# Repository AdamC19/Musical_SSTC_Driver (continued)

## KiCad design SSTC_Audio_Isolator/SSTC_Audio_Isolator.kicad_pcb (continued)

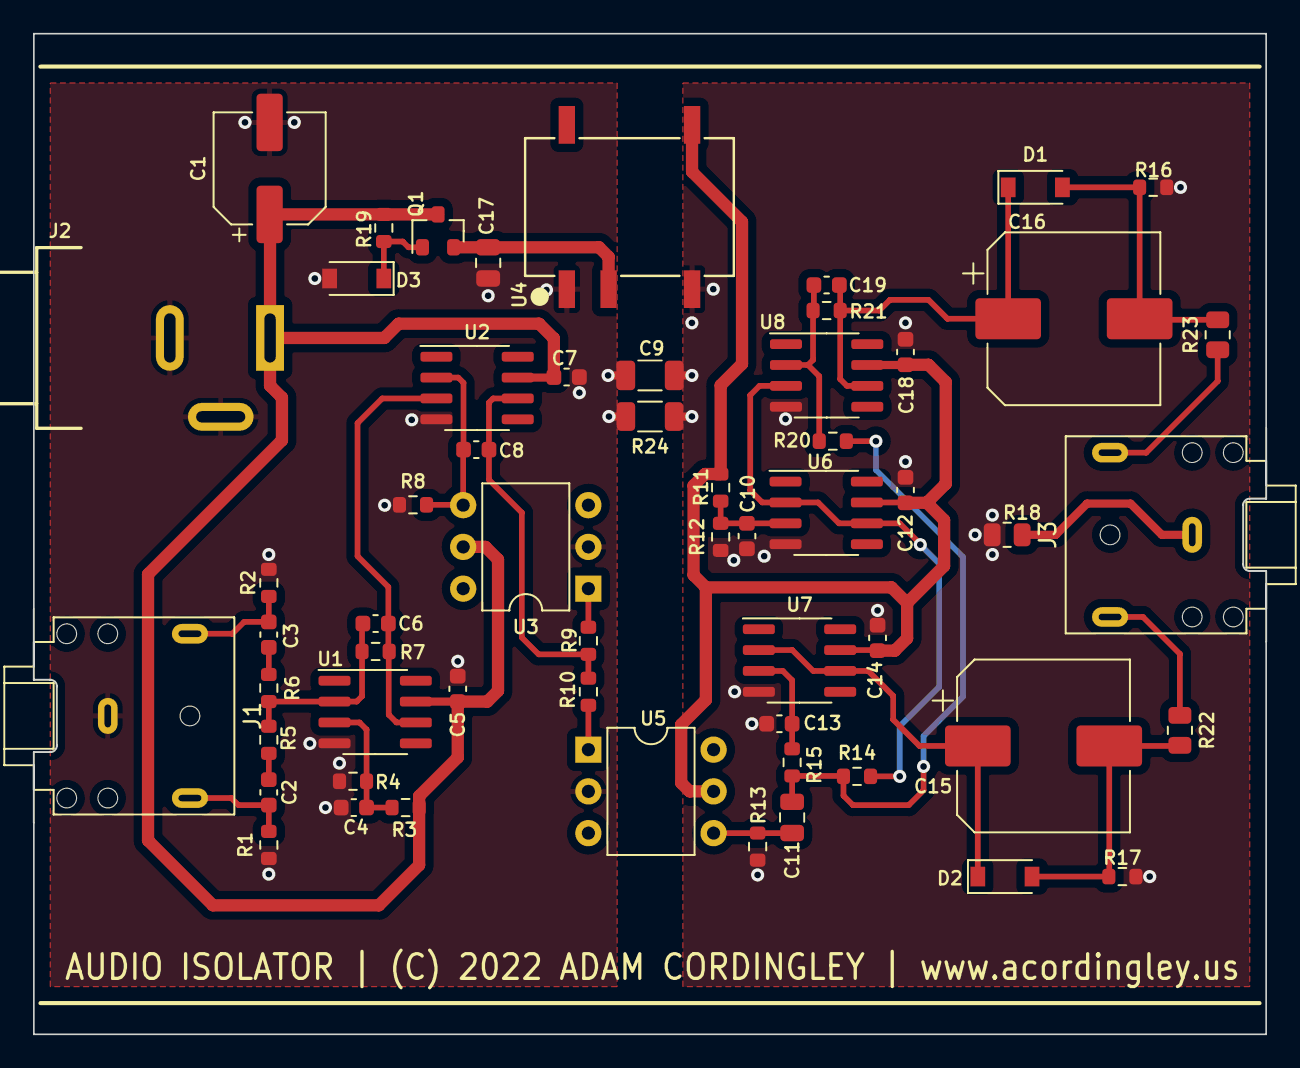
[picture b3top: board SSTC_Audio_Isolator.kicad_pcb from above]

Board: 2 copper layers, 75.0 x 60.9 mm, 58 parts (0 on the bottom side), 30 nets.

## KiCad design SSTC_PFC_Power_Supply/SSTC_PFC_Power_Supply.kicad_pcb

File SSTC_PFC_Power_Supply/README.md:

# APFC AC-DC Power Supply
This is an AC-to-DC power supply with Active Power Factor Correction (APFC). It takes in 120V AC and converts it to ~500V DC. It's designed to supply a maximum current of 1.8A, so about 900W. In case it needs to be said, this supply is dangerous! Don't build it unless you understand the risks and know how to mitigate them.

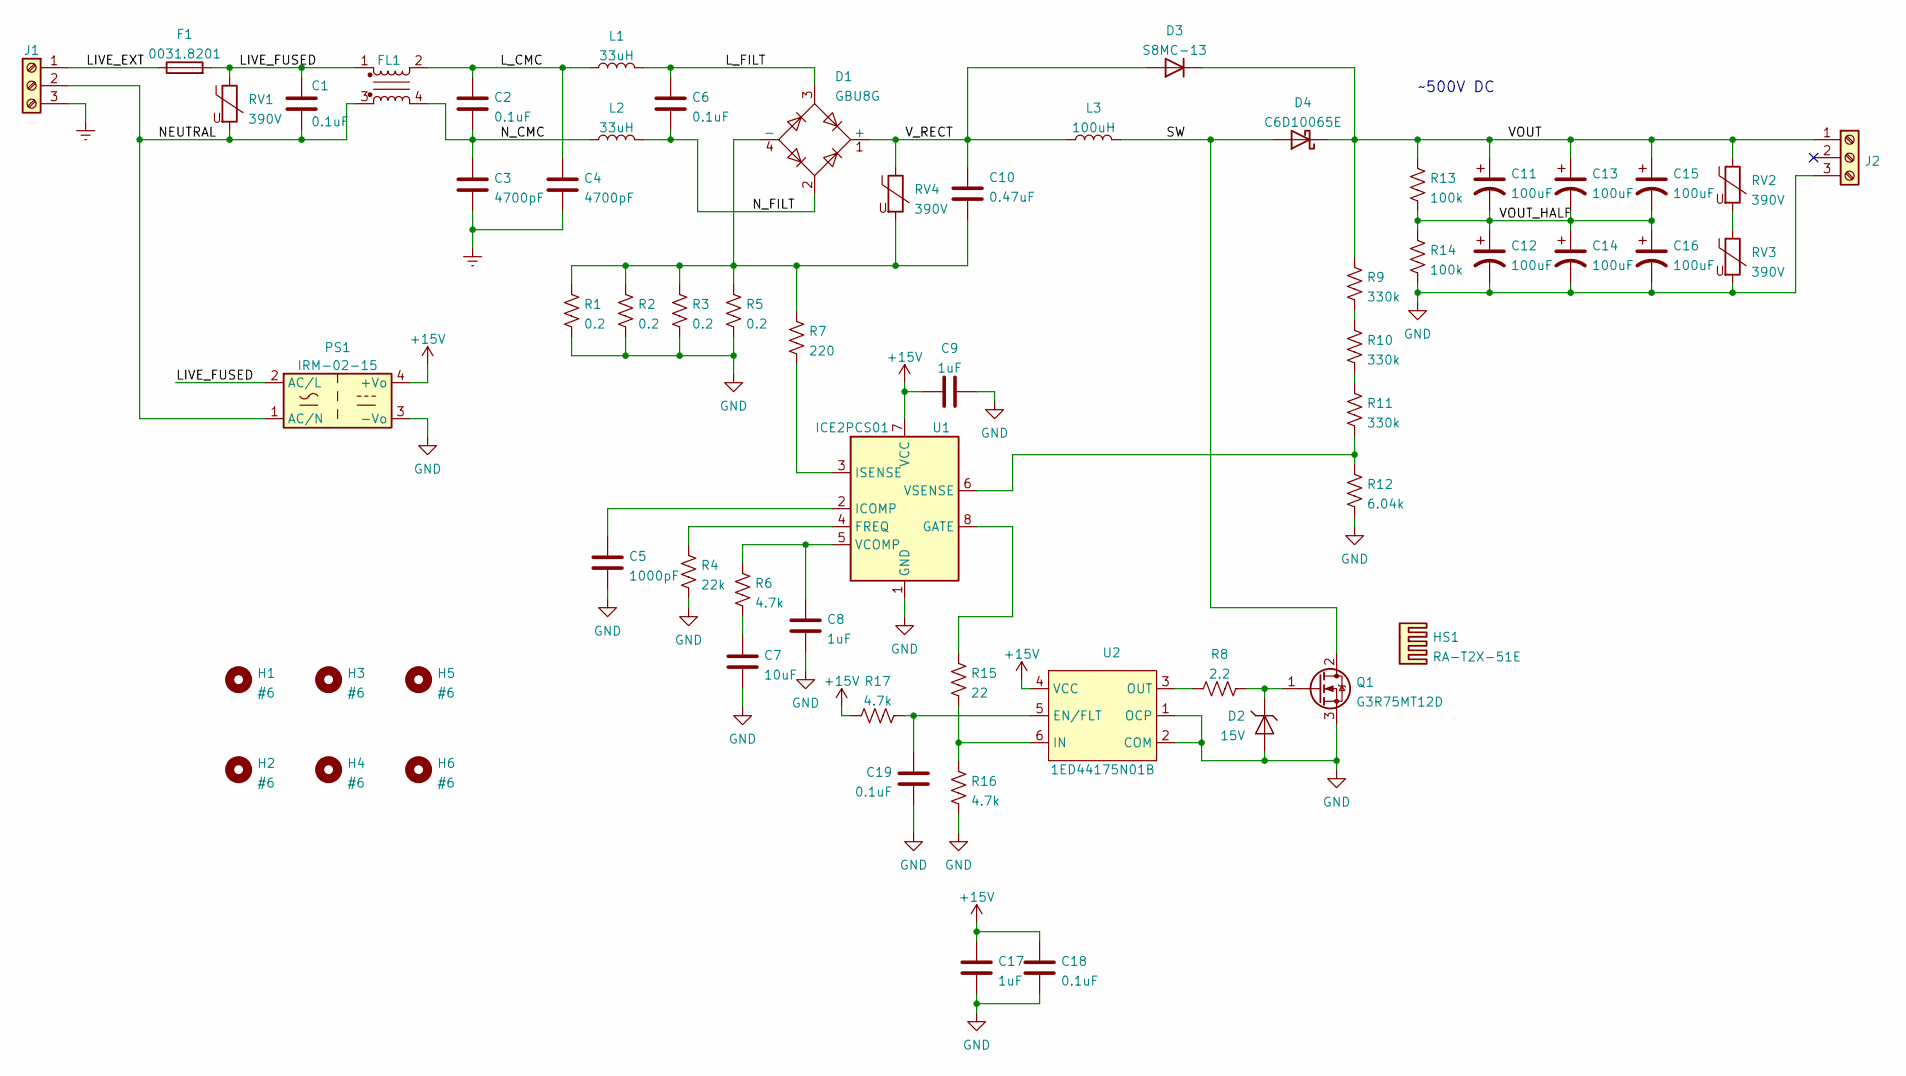
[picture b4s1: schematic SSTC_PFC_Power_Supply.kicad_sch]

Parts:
C1, C2, C6: 0.1uF; C_Rect_L18.0mm_W6.0mm_P15.00mm_FKS3_FKP3; MFG_PN PHE840MB6100MB05R17
C3, C4: 4700pF; C_Rect_L13.0mm_W4.0mm_P10.00mm_FKS3_FKP3_MKS4; MFG_PN R75PF1470AA01J
C5: 1000pF; C_0805_2012Metric
C7: 10uF; C_1206_3216Metric
C8, C9, C17: 1uF; C_0805_2012Metric
C10: 0.47uF; C_Rect_L18.0mm_W9.0mm_P15.00mm_FKS3_FKP3; MFG_PN B32922C3474K189
C11, C12, C13, C14, C15, C16: 100uF; CP_Radial_D18.0mm_P7.50mm; MFG_PN 450BXW100MEFR18X30
C18, C19: 0.1uF; C_0603_1608Metric
D1: GBU8G; Diode_Bridge_Vishay_GBU
D2: 15V; D_SOD-123
D3: S8MC-13; D_SMC; MFG_PN S8MC-13
D4: C6D10065E; TO-252-2_TabPin1_HV; MFG_PN C6D10065E
F1: 0031.8201; Fuseholder_Cylinder-5x20mm_Schurter_0031_8201_Horizontal_Op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; MFG_PN 0031.8201
FL1: 744824101; Weurth_WE-CMB; MFG_PN 744824101
H1, H2, H3, H4, H5, H6: #6; MountingHole_3.7mm_Pad
HS1: RA-T2X-51E; Ohmite_RA-T2X-51E; MFG_PN RA-T2X-51E
J1, J2: 1766246; PhoenixContact_GMSTBA_2,5_3-G-7,62_1x03_P7.62mm_Horizontal; MFG_PN 1766246
L1, L2: 33uH; L_Wuerth_HCI-2212; MFG_PN 74435583300
L3: 100uH; L_Bourns_1140-101K-RC; MFG_PN 1140-101K-RC
PS1: IRM-02-15; Converter_ACDC_MeanWell_IRM-02-xx_THT
Q1: G3R75MT12D; TO-247-3_Vertical; MFG_PN G3R75MT12D
R1, R2, R3, R5: 0.2; R_2512_6332Metric_High_Power; MFG_PN TLRP3A30CR200FTE
R4: 22k; R_0805_2012Metric
R6, R16, R17: 4.7k; R_0805_2012Metric
R7: 220; R_0805_2012Metric
R8: 2.2; R_0805_2012Metric
R9, R10, R11: 330k; R_1206_3216Metric
R12: 6.04k; R_0805_2012Metric
R13, R14: 100k; R_2512_6332Metric
R15: 22; R_0805_2012Metric
RV1, RV2, RV3, RV4: 390V; RV_Disc_D15.5mm_W4.9mm_P7.5mm; MFG_PN MOV-14D391K
U1: ICE2PCS01; SOIC-8_3.9x4.9mm_P1.27mm
U2: 1ED44175N01B; SOT-23-6; MFG_PN 1ED44175N01BXTSA1

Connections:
+15V: C9.2, C17.1, C18.1, PS1.4 (+Vo), R17.2, U1.7 (VCC), U2.4 (VCC)
/LIVE_EXT: F1.1, J1.1
/LIVE_FUSED: C1.1, F1.2, FL1.1, PS1.2 (AC/L), RV1.1
/L_CMC: C2.1, C4.1, FL1.2, L1.1
/L_FILT: C6.1, D1.3, L1.2
/NEUTRAL: C1.2, FL1.3, J1.2, PS1.1 (AC/N), RV1.2
/N_CMC: C2.2, C3.1, FL1.4, L2.1
/N_FILT: C6.2, D1.2, L2.2
/SW: D4.2 (A), L3.2, Q1.2 (D)
/VOUT: C11.1, C13.1, C15.1, D3.1 (K), D4.1 (K), J2.1, R9.2, R13.2, RV2.1
/VOUT_HALF: C11.2, C12.1, C13.2, C14.1, C15.2, C16.1, R13.1, R14.2
/V_RECT: C10.1, D1.1 (+), D3.2 (A), L3.1, RV4.1
Earth: C3.2, C4.2, J1.3
GND: C5.1, C7.1, C8.1, C9.1, C12.2, C14.2, C16.2, C17.2, C18.2, C19.2, D2.2 (A), J2.3, PS1.3 (-Vo), Q1.3 (S), R1.1, R2.1, R3.1, R4.1, R5.1, R12.1, R14.1, R16.1, RV3.2, U1.1 (GND), U2.1 (OCP), U2.2 (COM)
unnamed: C5.2, U1.2 (ICOMP)
unnamed: C7.2, R6.1
unnamed: C8.2, R6.2, U1.5 (VCOMP)
unnamed: C10.2, D1.4 (-), R1.2, R2.2, R3.2, R5.2, R7.2, RV4.2
unnamed: C19.1, R17.1, U2.5 (EN/FLT)
unnamed: D2.1 (K), Q1.1 (G), R8.1
unnamed: R4.2, U1.4 (FREQ)
unnamed: R7.1, U1.3 (ISENSE)
unnamed: R8.2, U2.3 (OUT)
unnamed: R10.1, R11.2
unnamed: R9.1, R10.2
unnamed: R11.1, R12.2, U1.6 (VSENSE)
unnamed: R15.1, U1.8 (GATE)
unnamed: R15.2, R16.2, U2.6 (IN)
unnamed: RV2.2, RV3.1

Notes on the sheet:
~500V DC

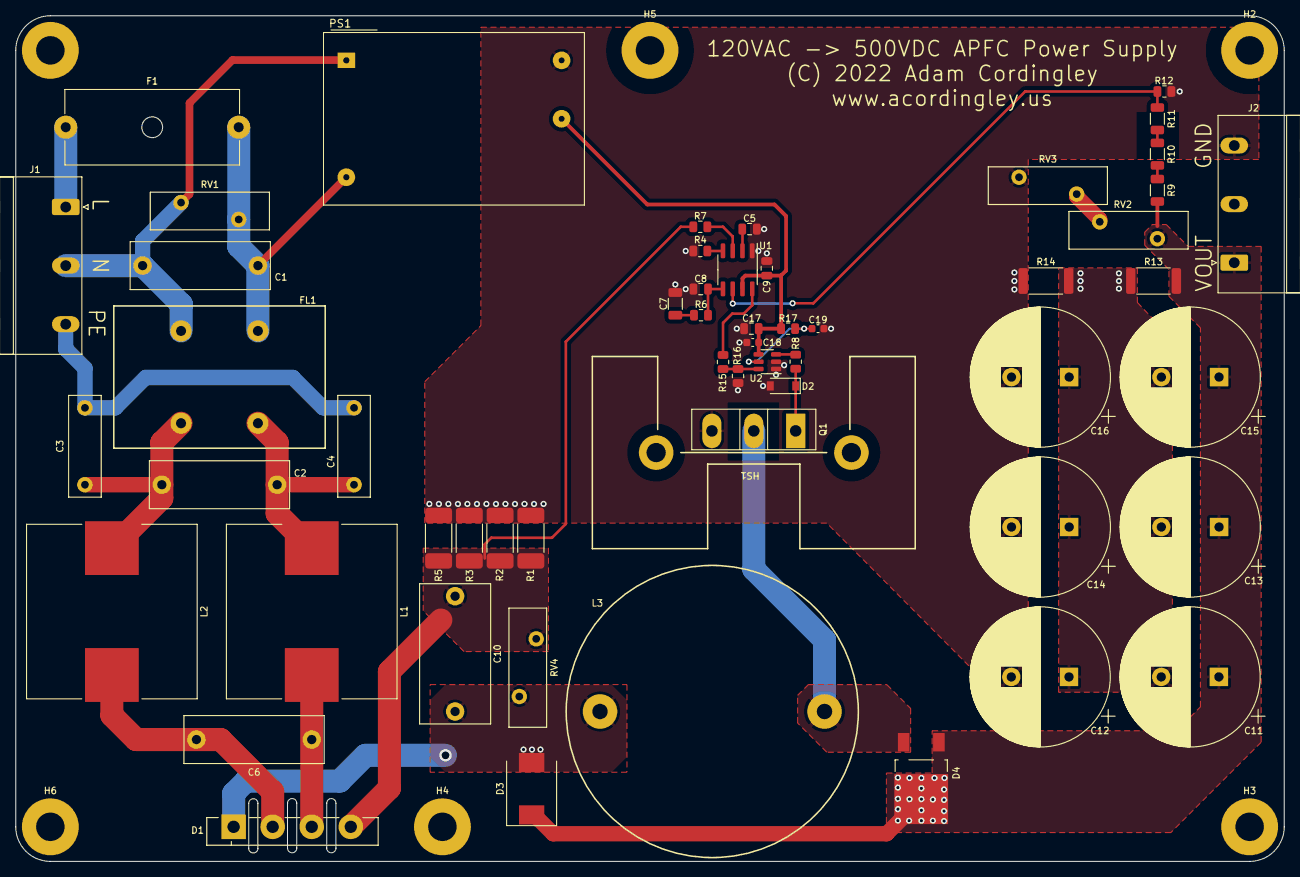
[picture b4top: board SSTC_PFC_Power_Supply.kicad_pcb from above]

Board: 2 copper layers, 165.0 x 110.0 mm, 62 parts (0 on the bottom side), 29 nets.

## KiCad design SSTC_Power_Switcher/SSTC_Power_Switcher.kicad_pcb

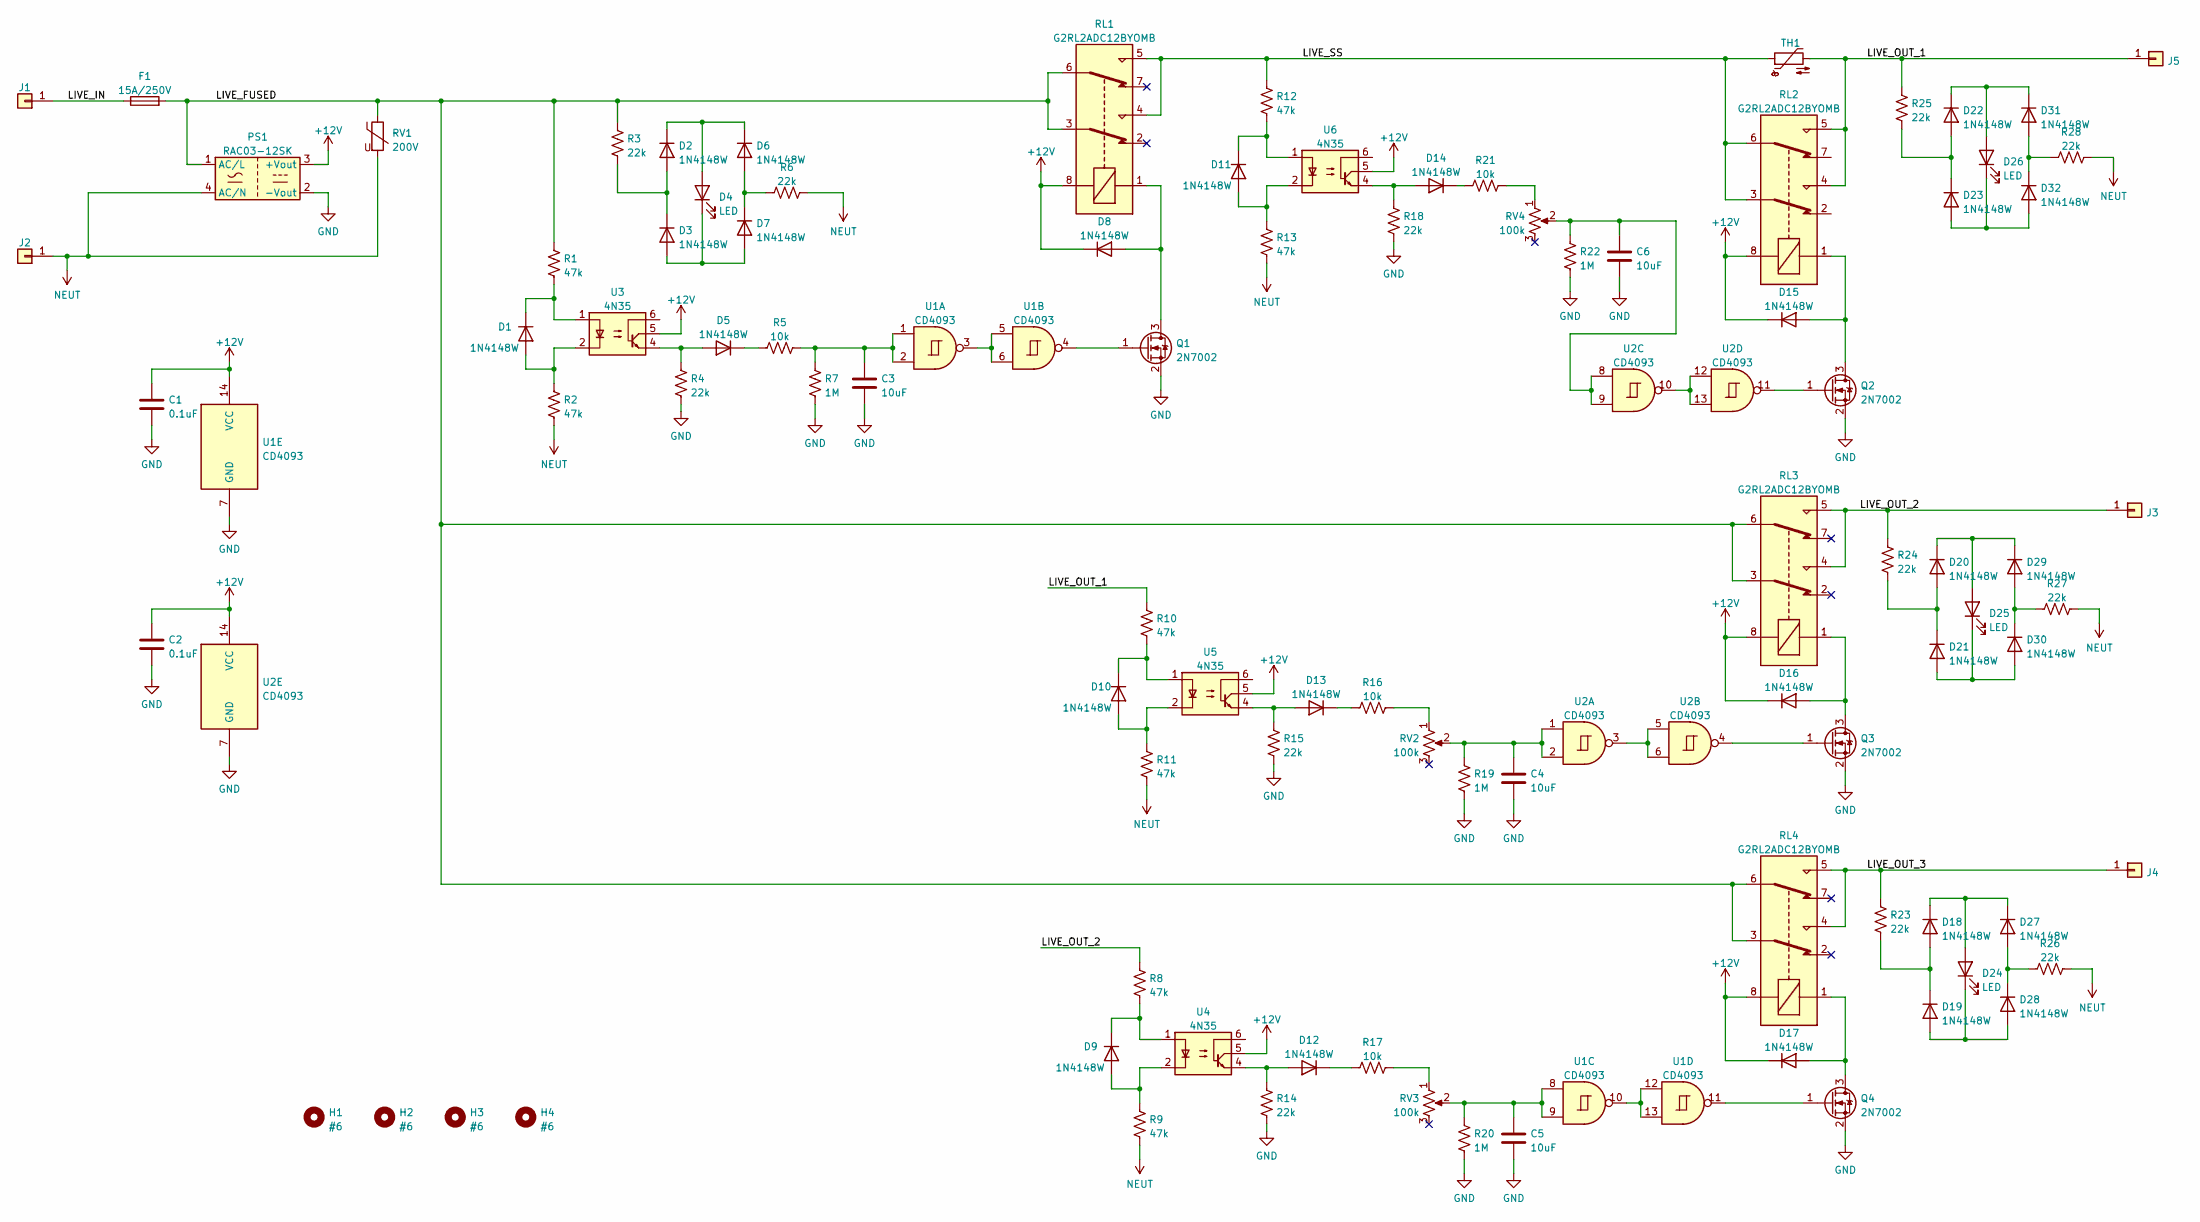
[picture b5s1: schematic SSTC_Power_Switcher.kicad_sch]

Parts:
C1, C2: 0.1uF; C_0603_1608Metric
C3, C4, C5, C6: 10uF; C_1206_3216Metric
D1, D2, D3, D5, D6, D7, D8, D9, D10, D11, D12, D13, D14, D15, D16, D17, D18, D19, D20, D21, D22, D23, D27, D28, D29, D30, D31, D32: 1N4148W; D_SOD-123
D4, D24, D25, D26: LED; LED_D5.0mm
F1: 15A/250V; Fuseholder_Littelfuse_100_series_5x20mm
H1, H2, H3, H4: #6; MountingHole_3.7mm
J1, J2, J3, J4, J5: Conn_01x01; TE_Connectivity_63824-1
PS1: RAC03-12SK; RAC03-K; MFG_PN RAC03-12SK
Q1, Q2, Q3, Q4: 2N7002; SOT-23
R1, R2, R8, R9, R10, R11, R12, R13: 47k; R_1206_3216Metric
R3, R6, R23, R24, R25, R26, R27, R28: 22k; R_1206_3216Metric
R4, R14, R15, R18: 22k; R_0805_2012Metric
R5, R16, R17, R21: 10k; R_0805_2012Metric
R7, R19, R20, R22: 1M; R_0805_2012Metric
RL1, RL2, RL3, RL4: G2RL2ADC12BYOMB; Relay_DPDT_Omron_G2RL; MFG_PN G2RL2ADC12BYOMB
RV1: 200V; RV_Disc_D12mm_W3.9mm_P7.5mm; MFG_PN MOV-10D201KTR
RV2, RV3, RV4: 100k; Potentiometer_Bourns_3386P_Vertical
TH1: Thermistor_NTC; RV_Disc_D21.5mm_W6.1mm_P7.5mm; MFG_PN SL22 20007
U1, U2: CD4093; SOIC-14_3.9x8.7mm_P1.27mm
U3, U4, U5, U6: 4N35; DIP-6_W7.62mm

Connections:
+12V: C1.1, C2.1, D8.1 (K), D15.1 (K), D16.1 (K), D17.1 (K), PS1.3 (+Vout), RL1.8, RL2.8, RL3.8, RL4.8, U1.14 (VCC), U2.14 (VCC), U3.5, U4.5, U5.5, U6.5
/LIVE_FUSED: F1.2, PS1.1 (AC/L), R1.1, R3.1, RL1.3, RL1.6, RL3.3, RL3.6, RL4.3, RL4.6, RV1.1
/LIVE_IN: F1.1, J1.1
/LIVE_OUT_1: J5.1, R10.1, R25.1, RL2.4, RL2.5, TH1.2
/LIVE_OUT_2: J3.1, R8.1, R24.1, RL3.4, RL3.5
/LIVE_OUT_3: J4.1, R23.1, RL4.4, RL4.5
/LIVE_SS: R12.1, RL1.4, RL1.5, RL2.3, RL2.6, TH1.1
GND: C1.2, C2.2, C3.2, C4.2, C5.2, C6.2, PS1.2 (-Vout), Q1.2 (S), Q2.2 (S), Q3.2 (S), Q4.2 (S), R4.2, R7.2, R14.2, R15.2, R18.2, R19.2, R20.2, R22.2, U1.7 (GND), U2.7 (GND)
NEUT: J2.1, PS1.4 (AC/N), R2.2, R6.2, R9.2, R11.2, R13.2, R26.2, R27.2, R28.2, RV1.2
unnamed: C3.1, R5.2, R7.1, U1.1, U1.2
unnamed: C4.1, R19.1, RV2.2, U2.1, U2.2
unnamed: C5.1, R20.1, RV3.2, U1.8, U1.9
unnamed: C6.1, R22.1, RV4.2, U2.8, U2.9
unnamed: D1.1 (K), R1.2, U3.1
unnamed: D1.2 (A), R2.1, U3.2
unnamed: D2.1 (K), D4.2 (A), D6.1 (K)
unnamed: D2.2 (A), D3.1 (K), R3.2
unnamed: D3.2 (A), D4.1 (K), D7.2 (A)
unnamed: D5.1 (K), R5.1
unnamed: D5.2 (A), R4.1, U3.4
unnamed: D6.2 (A), D7.1 (K), R6.1
unnamed: D8.2 (A), Q1.3 (D), RL1.1
unnamed: D9.1 (K), R8.2, U4.1
unnamed: D9.2 (A), R9.1, U4.2
unnamed: D10.1 (K), R10.2, U5.1
unnamed: D10.2 (A), R11.1, U5.2
unnamed: D11.1 (K), R12.2, U6.1
unnamed: D11.2 (A), R13.1, U6.2
unnamed: D12.1 (K), R17.1
unnamed: D12.2 (A), R14.1, U4.4
unnamed: D13.1 (K), R16.1
unnamed: D13.2 (A), R15.1, U5.4
unnamed: D14.1 (K), R21.1
unnamed: D14.2 (A), R18.1, U6.4
unnamed: D15.2 (A), Q2.3 (D), RL2.1
unnamed: D16.2 (A), Q3.3 (D), RL3.1
unnamed: D17.2 (A), Q4.3 (D), RL4.1
unnamed: D18.1 (K), D24.2 (A), D27.1 (K)
unnamed: D18.2 (A), D19.1 (K), R23.2
unnamed: D19.2 (A), D24.1 (K), D28.2 (A)
unnamed: D20.1 (K), D25.2 (A), D29.1 (K)
unnamed: D20.2 (A), D21.1 (K), R24.2
unnamed: D21.2 (A), D25.1 (K), D30.2 (A)
unnamed: D22.1 (K), D26.2 (A), D31.1 (K)
unnamed: D22.2 (A), D23.1 (K), R25.2
unnamed: D23.2 (A), D26.1 (K), D32.2 (A)
unnamed: D27.2 (A), D28.1 (K), R26.1
unnamed: D29.2 (A), D30.1 (K), R27.1
unnamed: D31.2 (A), D32.1 (K), R28.1
unnamed: Q1.1 (G), U1.4
unnamed: Q2.1 (G), U2.11
unnamed: Q3.1 (G), U2.4
unnamed: Q4.1 (G), U1.11
unnamed: R16.2, RV2.1
unnamed: R17.2, RV3.1
unnamed: R21.2, RV4.1
unnamed: U1.3, U1.5, U1.6
unnamed: U1.10, U1.12, U1.13
unnamed: U2.3, U2.5, U2.6
unnamed: U2.10, U2.12, U2.13

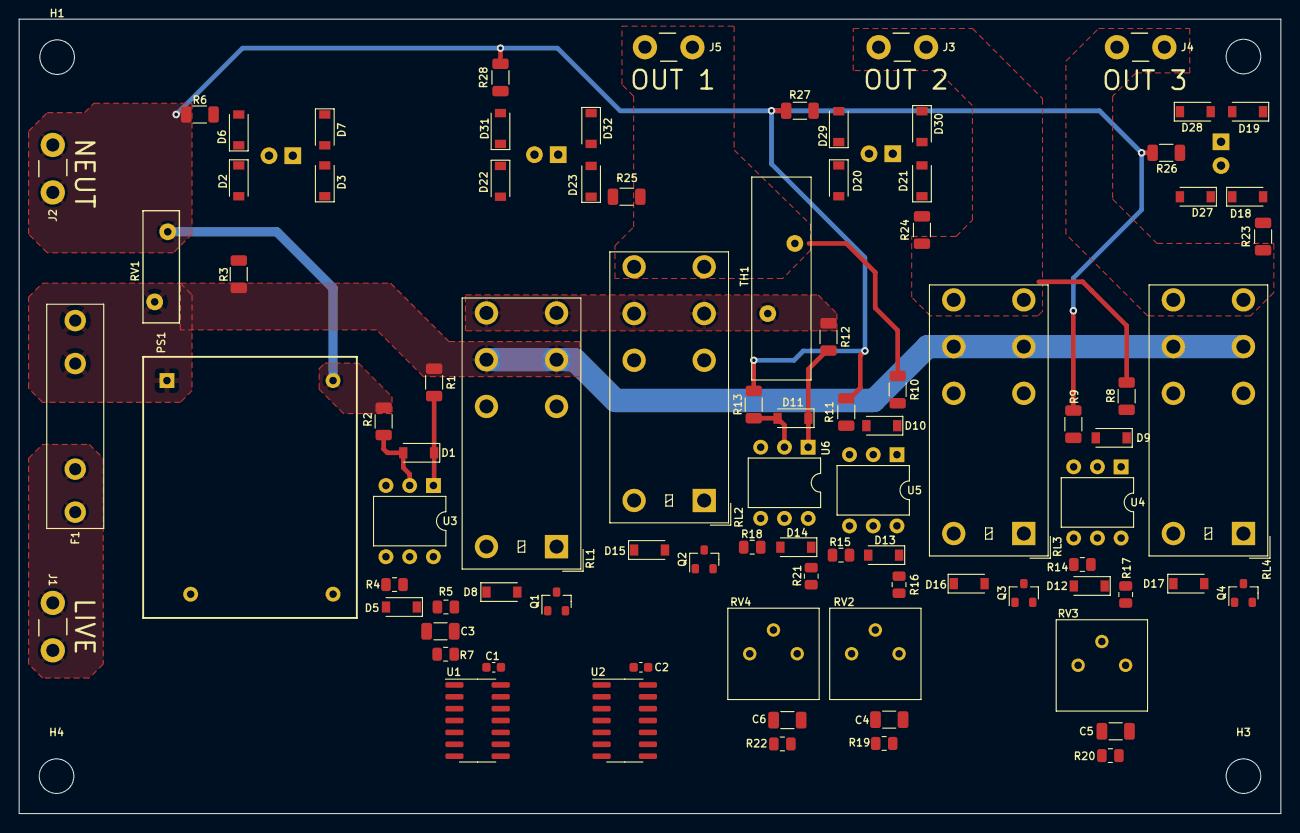
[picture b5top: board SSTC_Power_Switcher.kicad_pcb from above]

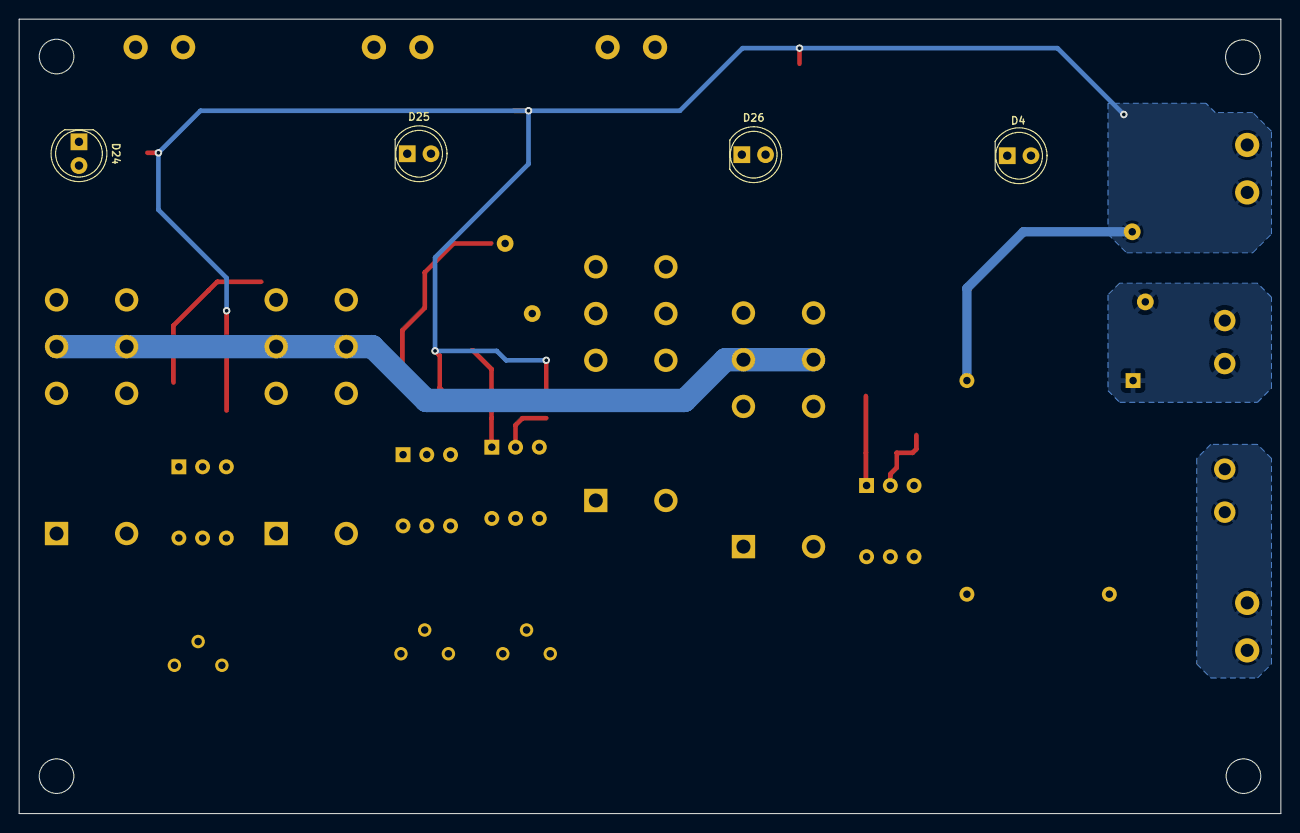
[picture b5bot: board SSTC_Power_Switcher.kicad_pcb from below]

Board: 2 copper layers, 135.0 x 85.0 mm, 96 parts (4 on the bottom side), 60 nets.

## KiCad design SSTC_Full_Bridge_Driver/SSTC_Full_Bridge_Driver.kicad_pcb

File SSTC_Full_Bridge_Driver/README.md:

# Full-Bridge Driver
See below a simplified schematic of the full-bridge driver.

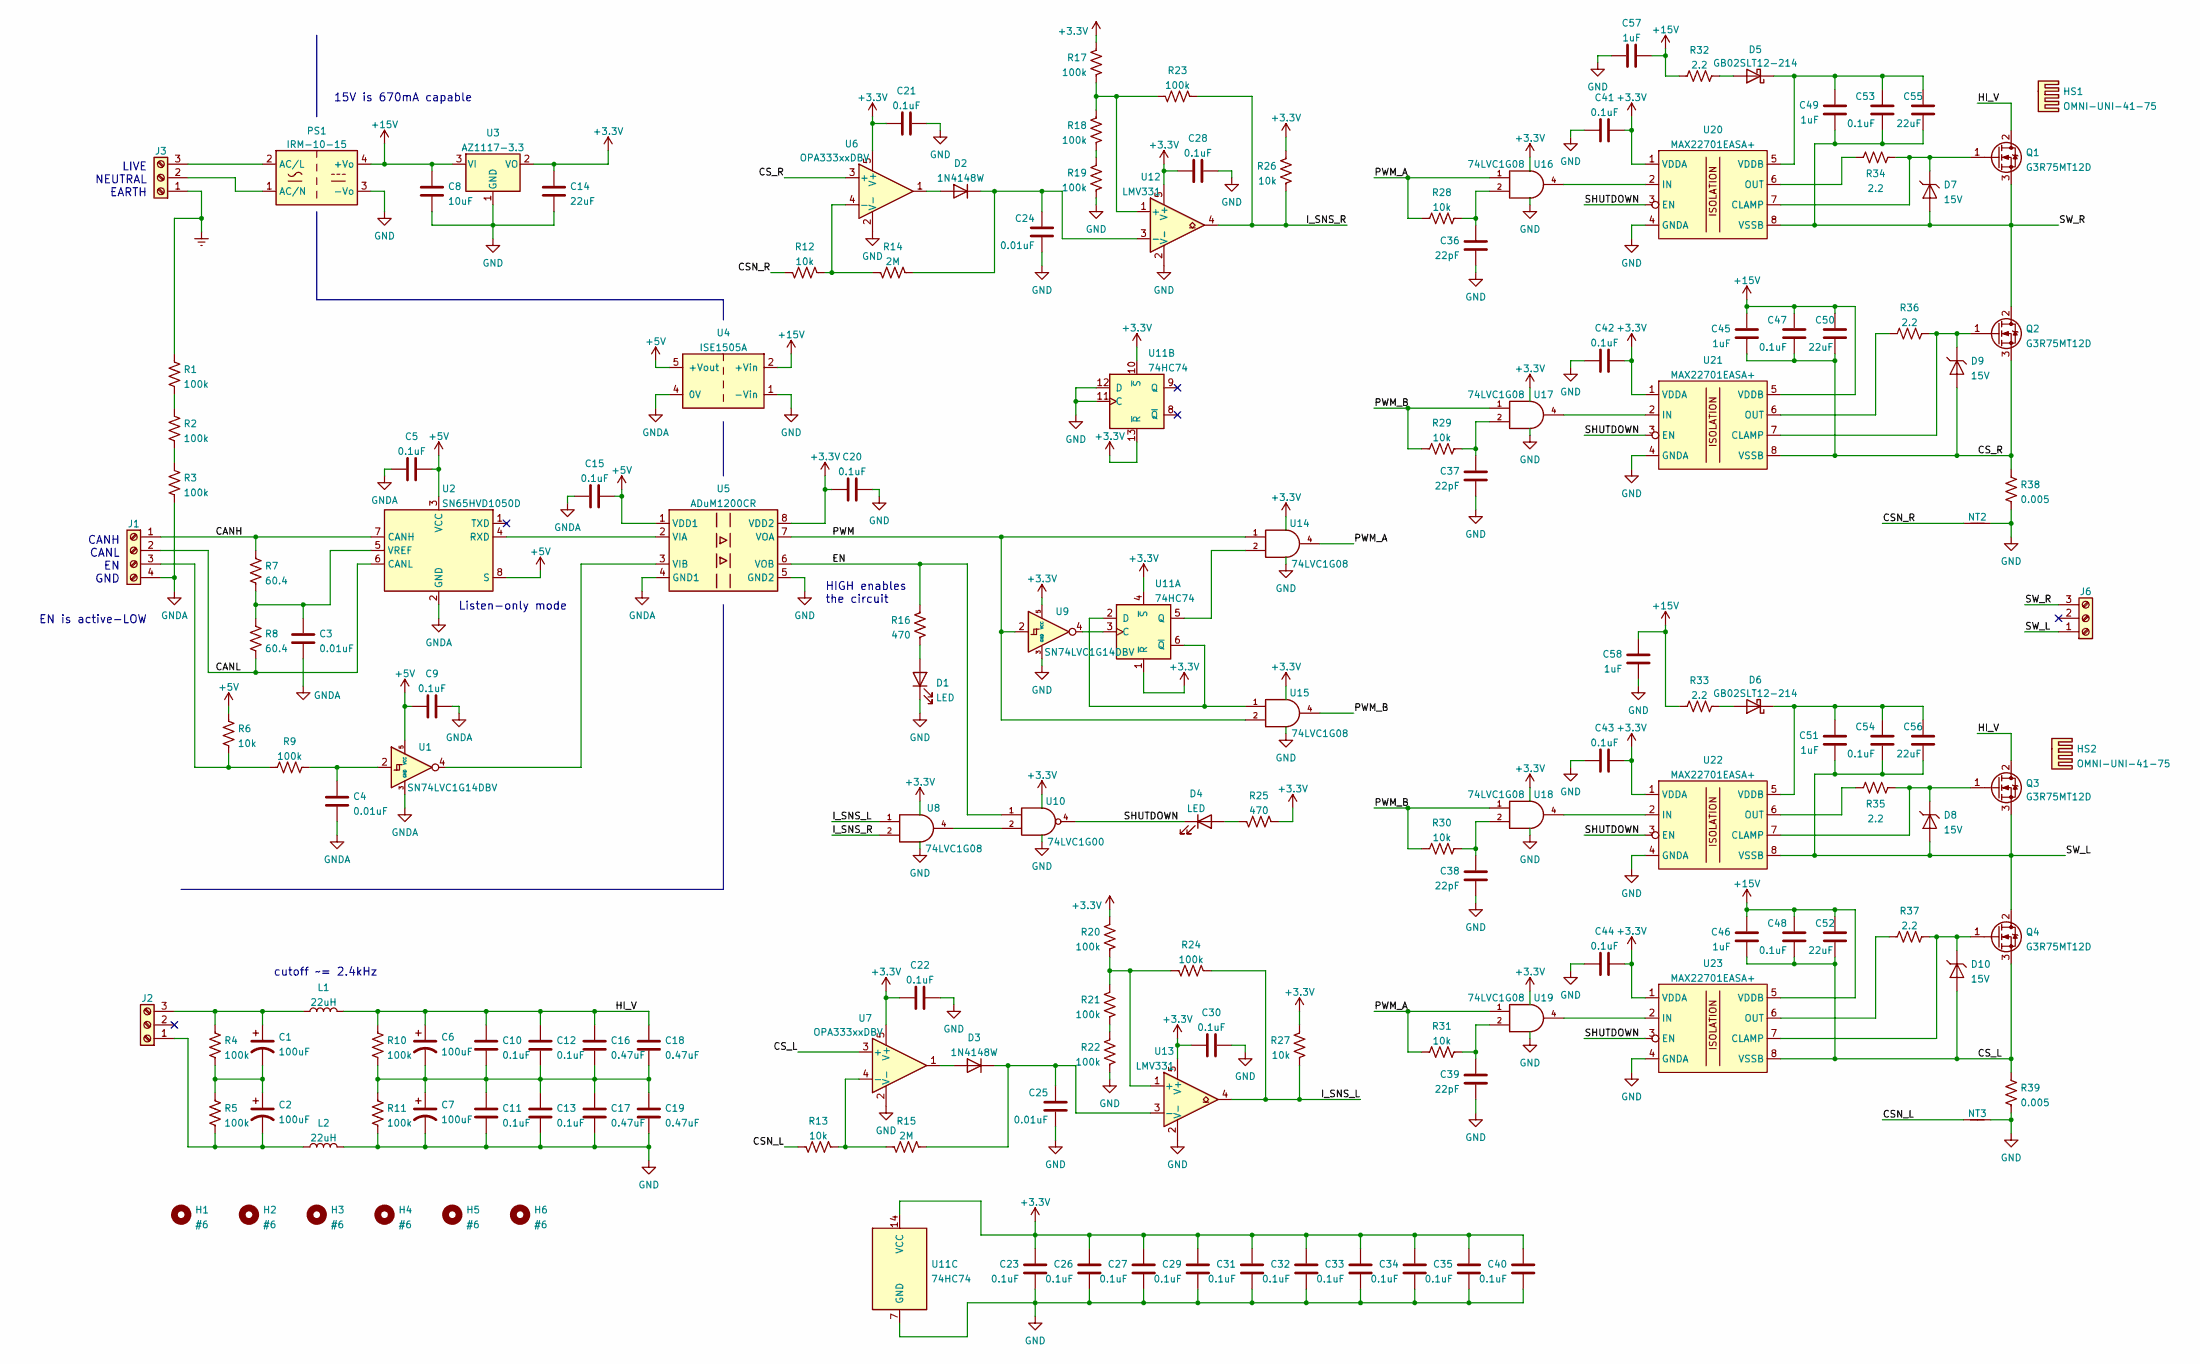
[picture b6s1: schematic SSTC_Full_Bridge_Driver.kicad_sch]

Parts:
C1, C2, C6, C7: 100uF; CP_Radial_D18.0mm_P7.50mm; MFG_PN 450BXW100MEFR18X30
C3, C4, C24, C25: 0.01uF; C_0603_1608Metric
C5, C9, C15, C20, C21, C22, C23, C26, C27, C28, C29, C30, C31, C32, C33, C34, C35, C40, C41, C42, C43, C44, C47, C48, C53, C54: 0.1uF; C_0603_1608Metric
C8: 10uF; C_1206_3216Metric
C10, C11, C12, C13: 0.1uF; C_1812_4532Metric; MFG_PN C4532X7R2J104K230KA
C14, C50, C52, C55, C56: 22uF; C_1206_3216Metric
C16, C17, C18, C19: 0.47uF; C_1812_4532Metric; MFG_PN C4532X7T2W474K230KA
C36, C37, C38, C39: 22pF; C_0603_1608Metric
C45, C46, C49, C51, C57, C58: 1uF; C_0805_2012Metric
D1, D4: LED; LED_0603_1608Metric
D2, D3: 1N4148W; D_SOD-123
D5, D6: GB02SLT12-214; D_SMB
D7, D8, D9, D10: 15V; D_SOD-123
H1, H2, H3, H4, H5, H6: #6; MountingHole_3.7mm_Pad
HS1, HS2: OMNI-UNI-41-75; Wakefield_Vette_OMNI-UNI-41-75; MFG_PN OMNI-UNI-41-75
J1: Screw_Terminal_01x04; PhoenixContact_MC_1,5_4-G-3.81_1x04_P3.81mm_Horizontal
J2, J3, J6: Screw_Terminal_01x03; PhoenixContact_GMSTBA_2,5_3-G-7,62_1x03_P7.62mm_Horizontal
L1, L2: 22uH; L_Wuerth_WE-PD-Typ-LS; MFG_PN 7447709220
NT2, NT3: NetTie_2; NetTie-2_SMD_Pad0.5mm
PS1: IRM-10-15; Converter_ACDC_MeanWell_IRM-10-xx_THT
Q1, Q2, Q3, Q4: G3R75MT12D; TO-247-3_Vertical; MFG_PN G3R75MT12D
R1, R2, R3, R9, R17, R18, R19, R20, R21, R22, R23, R24: 100k; R_0805_2012Metric
R4, R5, R10, R11: 100k; R_2512_6332Metric
R6, R12, R13, R26, R27, R28, R29, R30, R31: 10k; R_0805_2012Metric
R7, R8: 60.4; R_0805_2012Metric
R14, R15: 2M; R_0805_2012Metric
R16, R25: 470; R_0805_2012Metric
R32, R33, R34, R35, R36, R37: 2.2; R_0805_2012Metric
R38, R39: 0.005; R_1206_3216Metric
U1, U9: SN74LVC1G14DBV; SOT-23-5
U2: SN65HVD1050D; SOIC-8_3.9x4.9mm_P1.27mm
U3: AZ1117-3.3; SOT-89-3
U4: ISE1505A; XP_Power_ISE
U5: ADuM1200CR; SOIC-8_3.9x4.9mm_P1.27mm
U6, U7: OPA333xxDBV; SOT-23-5
U8, U14, U15, U16, U17, U18, U19: 74LVC1G08; SOT-23-5
U10: 74LVC1G00; SOT-23-5
U11: 74HC74; SOIC-14_3.9x8.7mm_P1.27mm
U12, U13: LMV331; SOT-23-5
U20, U21, U22, U23: MAX22701EASA+; SOIC-8_3.9x4.9mm_P1.27mm

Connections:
+3V3: C14.1, C20.1, C21.2, C22.2, C23.2, C26.2, C27.2, C28.2, C29.2, C30.2, C31.2, C32.2, C33.2, C34.2, C35.2, C40.2, C41.2, C42.2, C43.2, C44.2, R17.2, R20.2, R25.2, R26.2, R27.2, U3.2 (VO), U5.8 (VDD2), U6.5 (V+), U7.5 (V+), U8.5 (VCC), U9.5 (VCC), U10.5 (VCC), U11.1 (~R), U11.4 (~S), U11.10 (~S), U11.13 (~R), U11.14 (VCC), U12.5 (V+), U13.5 (V+), U14.5 (VCC), U15.5 (VCC), U16.5 (VCC), U17.5 (VCC), U18.5 (VCC), U19.5 (VCC), U20.1 (VDDA), U21.1 (VDDA), U22.1 (VDDA), U23.1 (VDDA)
+5V: C5.2, C9.1, C15.1, R6.1, U1.5 (VCC), U2.3 (VCC), U2.8 (S), U4.5 (+Vout), U5.1 (VDD1)
+15V: C8.1, C45.2, C46.2, C47.2, C48.2, C50.2, C52.2, C57.1, C58.2, PS1.4 (+Vo), R32.1, R33.1, U3.3 (VI), U4.2 (+Vin), U21.5 (VDDB), U23.5 (VDDB)
/CANH: J1.1, R7.1, U2.7 (CANH)
/CANL: J1.2, R8.2, U2.6 (CANL)
/CSN_L: NT3.1, R13.2
/CSN_R: NT2.1, R12.2
/CS_L: C46.1, C48.1, C52.1, D10.2 (A), Q4.3 (S), R39.2, U7.3 (+), U23.8 (VSSB)
/CS_R: C45.1, C47.1, C50.1, D9.2 (A), Q2.3 (S), R38.2, U6.3 (+), U21.8 (VSSB)
/EN: R16.2, U5.6 (VOB), U10.1
/HI_V: C6.1, C10.2, C12.2, C16.2, C18.2, L1.2, Q1.2 (D), Q3.2 (D), R10.1
/I_SNS_L: R24.2, R27.1, U8.1, U13.4
/I_SNS_R: R23.2, R26.1, U8.2, U12.4
/PWM: U5.7 (VOA), U9.2, U14.1, U15.2
/PWM_A: R28.1, R31.1, U14.4, U16.1, U19.1
/PWM_B: R29.1, R30.1, U15.4, U17.1, U18.1
/SHUTDOWN: D4.1 (K), U10.4, U20.3 (EN), U21.3 (EN), U22.3 (EN), U23.3 (EN)
/SW_L: C51.1, C54.1, C56.1, D8.2 (A), J6.1, Q3.3 (S), Q4.2 (D), U22.8 (VSSB)
/SW_R: C49.1, C53.1, C55.1, D7.2 (A), J6.3, Q1.3 (S), Q2.2 (D), U20.8 (VSSB)
Earth: J3.1, R1.1
GND: C7.2, C8.2, C11.1, C13.1, C14.2, C17.1, C19.1, C20.2, C21.1, C22.1, C23.1, C24.1, C25.1, C26.1, C27.1, C28.1, C29.1, C30.1, C31.1, C32.1, C33.1, C34.1, C35.1, C36.1, C37.1, C38.1, C39.1, C40.1, C41.1, C42.1, C43.1, C44.1, C57.2, C58.1, D1.1 (K), L2.2, NT2.2, NT3.2, PS1.3 (-Vo), R11.2, R19.1, R22.1, R38.1, R39.1, U3.1 (GND), U4.1 (-Vin), U5.5 (GND2), U6.2 (V-), U7.2 (V-), U8.3 (GND), U9.3 (GND), U10.3 (GND), U11.7 (GND), U11.11 (C), U11.12 (D), U12.2 (V-), U13.2 (V-), U14.3 (GND), U15.3 (GND), U16.3 (GND), U17.3 (GND), U18.3 (GND), U19.3 (GND), U20.4 (GNDA), U21.4 (GNDA), U22.4 (GNDA), U23.4 (GNDA)
GNDA: C3.1, C4.1, C5.1, C9.2, C15.2, J1.4, R3.2, U1.3 (GND), U2.2 (GND), U4.4 (0V), U5.4 (GND1)
unnamed: C1.1, J2.3, L1.1, R4.1
unnamed: C1.2, C2.1, R4.2, R5.1
unnamed: C2.2, J2.1, L2.1, R5.2
unnamed: C3.2, R7.2, R8.1, U2.5 (VREF)
unnamed: C4.2, R9.2, U1.2
unnamed: C6.2, C7.1, C10.1, C11.2, C12.1, C13.2, C16.1, C17.2, C18.1, C19.2, R10.2, R11.1
unnamed: C24.2, D2.1 (K), R14.1, U12.3 (-)
unnamed: C25.2, D3.1 (K), R15.1, U13.3 (-)
unnamed: C36.2, R28.2, U16.2
unnamed: C37.2, R29.2, U17.2
unnamed: C38.2, R30.2, U18.2
unnamed: C39.2, R31.2, U19.2
unnamed: C49.2, C53.2, C55.2, D5.1 (K), U20.5 (VDDB)
unnamed: C51.2, C54.2, C56.2, D6.1 (K), U22.5 (VDDB)
unnamed: D1.2 (A), R16.1
unnamed: D2.2 (A), U6.1
unnamed: D3.2 (A), U7.1
unnamed: D4.2 (A), R25.1
unnamed: D7.1 (K), Q1.1 (G), R34.2, U20.7 (CLAMP)
unnamed: D8.1 (K), Q3.1 (G), R35.2, U22.7 (CLAMP)
unnamed: D9.1 (K), Q2.1 (G), R36.2, U21.7 (CLAMP)
unnamed: D10.1 (K), Q4.1 (G), R37.2, U23.7 (CLAMP)
unnamed: J1.3, R6.2, R9.1
unnamed: J3.2, PS1.1 (AC/N)
unnamed: J3.3, PS1.2 (AC/L)
unnamed: R1.2, R2.1
unnamed: R2.2, R3.1
unnamed: R12.1, R14.2, U6.4 (-)
unnamed: R13.1, R15.2, U7.4 (-)
unnamed: R17.1, R18.2, R23.1, U12.1 (+)
unnamed: R18.1, R19.2
unnamed: R20.1, R21.2, R24.1, U13.1 (+)
unnamed: R21.1, R22.2
unnamed: D5.2 (A), R32.2
unnamed: D6.2 (A), R33.2
unnamed: R34.1, U20.6 (OUT)
unnamed: R35.1, U22.6 (OUT)
unnamed: R36.1, U21.6 (OUT)
unnamed: R37.1, U23.6 (OUT)
unnamed: U1.4, U5.3 (VIB)
unnamed: U2.4 (RXD), U5.2 (VIA)
unnamed: U8.4, U10.2
unnamed: U11.2 (D), U11.6 (~Q), U15.1
unnamed: U9.4, U11.3 (C)
unnamed: U11.5 (Q), U14.2
unnamed: U16.4, U20.2 (IN)
unnamed: U17.4, U21.2 (IN)
unnamed: U18.4, U22.2 (IN)
unnamed: U19.4, U23.2 (IN)

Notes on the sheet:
CANH CANL EN GND
EN is active-LOW
15V is 670mA capable
cutoff ~= 2.4kHz
Listen-only mode
HIGH enables the circuit
LIVE NEUTRAL EARTH

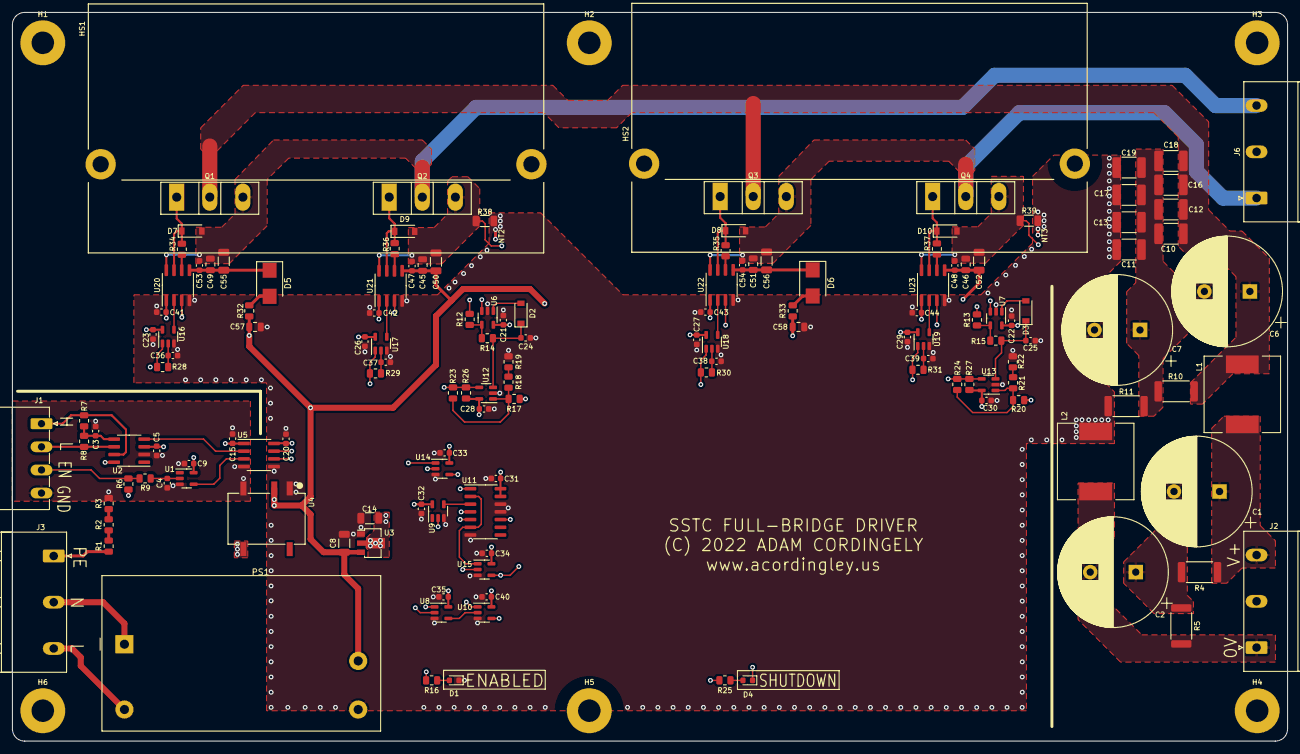
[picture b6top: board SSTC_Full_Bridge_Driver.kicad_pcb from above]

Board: 4 copper layers, 210.0 x 120.0 mm, 151 parts (0 on the bottom side), 71 nets.
